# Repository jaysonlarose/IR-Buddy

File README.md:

# IR-Buddy

A Thing That Does IR Remote Stuff.

## Easy To Use

IR-Buddy presents itself to a host computer as a USB Serial device and uses a simple, straightforward ASCII protocol. You can open up the device using a terminal emulator and get started right away, or you can build it into an automation system. Capturing and replaying an IR code is as easy as pointing the remote at IR-Buddy, hitting the button, and copy-pasting the output back into the terminal.

## Smart, But Not Too Smart

IR-Buddy has a couple of power features for those that want to use them. It understands the concept of codes that repeat a certain sequence when the button is held down, to make tasks like changing volume go more smoothly. The output frequency can be tweaked to a certain extent to satisfy receivers that may be slightly finicky. It has screw terminals to accept up to eight emitter LEDs, which can be individually enabled or disabled, handy for when you have multiple devices that react to the same code. All of these features are completely optional.

What do I mean by "not too smart"? IR-buddy doesn't have a concept of what *type* of code it's sending or receiving. It doesn't know NEC protocol from JVC protocol from RC5. It just sees a bunch of ON-OFF transitions, and that's what it gives you. When you want to send a code, you tell it the timing of how to send these ON-OFF transitions, and it'll do it. If you want to get fancy with interpreting or synthesizing these ON-OFF timing pairs, that's your prerogative.

## Protocol Details

IR-buddy communicates as a standard USB Serial device using the ASCII character set. Line termination is UNIX-style, using just the linefeed character (0x0a). You may need to fiddle around with your terminal emulator software to get this dialed in.

### IR Reception

Whenever IR-Buddy isn't actively receiving a code to send or sending one, it's monitoring the IR receiver for activity. When it finishes receiving one, it will print out a message that looks like this:

```
IR <ondur> <offdur> <ondur> <offdur> <...> <ondur>\n
```

`<ondur>` is the length of time that the modulated IR carrier was detected ("MARK" time), in microseconds.

`<offdur>` is the length of time that the modulated IR carrier was absent ("SPACE" time), in microseconds.

Example

I've got a CRT TV. It's an Advent somethingorother that I bought off eBay. It didn't come with a remote, so I had to buy one off eBay as well, but I digress. When I point the remote at the IR-buddy and give the power button a good press, I get:

```
IR 15866 450 1650 500 1650 500 1650 500 550 500 550 500 550 500 1650 500 550 500 550 500 1650 500 550 500 550 500 550 450 600 500 550 500 550 600
IR 22850 500 1650 450 1700 500 1650 500 500 500 550 500 550 500 1650 500 550 500 550 500 1650 500 550 500 550 500 550 500 550 500 550 500 550 600
IR 22800 500 1650 500 1650 500 1650 500 550 500 550 500 550 500 1650 500 550 500 550 500 1650 500 550 500 550 500 550 450 600 500 550 500 500 650
IR 22800 500 1650 500 1650 500 1650 500 550 500 550 500 550 500 1650 500 500 500 550 500 1650 500 550 500 550 500 550 500 550 500 550 500 550 600
IR 22850 500 1650 500 1650 500 1650 500 550 500 500 500 550 500 1650 500 550 500 550 500 1650 500 550 500 550 500 550 500 550 500 550 500 550 600
```

(And the TV turns on.) Yes, five separate lines. Remote controls tend to be fairly chatty when you press the button, and the Arduino-IRremote library that powers IR-buddy splits out any code sequence with a gap longer than about 5 milliseconds into a separate transmission.

What you're looking at is a list of timings. All values are in microseconds.

The first number after "IR" is the amount of time since the end of the last detected transmission. This is provided for when you need to combine multiple transmissions together into a single code. I happen to know a bit about this TV, and that's exactly what we're going to need to do here, as I'll explain in a bit. But first, let's discuss the rest of the line.

The next number is the "mark" time. The number of microseconds that the 38KHz infrared carrier was detected. The next number is the "space" time, the duration of time that no carrier is being sent. After that is another "mark" time. Then another "space" time. And so on.

As I mentioned, I know a bit about this TV, and I know that you need to send a code at least twice to get it to pay attention to you. So we're going to combine two of these codes together. Take the first line, and remove the "IR" from the start of it along with the first number. Then, take the second line (minus the initial "IR") and add it to the end of the first line, like so:

```
1650 500 1650 500 1650 500 550 500 550 500 550 500 1650 500 550 500 550 500 1650 500 550 500 550 500 550 450 600 500 550 500 550 600 22850 500 1650 450 1700 500 1650 500 500 500 550 500 550 500 1650 500 550 500 550 500 1650 500 550 500 550 500 550 500 550 500 550 500 550 600
```

Copy and paste this line back into the terminal emulator. You may need to press "enter" at the end as well. You should get back a line saying "RX OK". And if you're me, your TV will turn back off.

### IR Transmission

Well, we already sent our first IR code in the previous section, but I'll go into more detail here. In its simplest form, sending an IR code is just a matter of entering a quantity of "on duration", "off duration" numbers, separated by spaces, followed by a newline (aka pressing "return").

As soon as you enter a numeric character, IR-buddy will print out "RX " followed by the quantity of timing values entered thusfar. Each time you press space to start a new timing value, it will update the quantity. When you press return, it will respond with "OK" followed by a newline and transmit the code.

#### Repeat Codes

Most remotes have some sort of method of telling the thing on the other end of the room that a button is being held down. Sure, you can just send the code over and over again, but it just won't be as seamless as being able to act like the original. That's where repeat codes come in.

A ton of remotes use what's called the NEC protocol (or one of derivatives of the NEC protocol). Long story short, codes start with a 9 millisecond "attention" mark, followed by 4.5 milliseconds of space, then approximately 54 milliseconds of the actual remote data. As long as the button that initiated the code is held down, the remote announces this by sending an additional set of (9ms mark, 2.25ms space, 560 microsecond mark) every 110 milliseconds.

Here's what this looks like from IR-Buddy's perspective, using the "volume up" button on an old LG television remote as an example:

```
IR 434500 9050 4500 600 500 600 550 600 1650 600 500 600 550 600 550 600 500 600 550 600 1650 600 1650 600 500 600 1650 600 1650 600 1650 600 1650 600 1650 600 550 600 1650 600 550 600 500 600 550 600 500 600 550 600 550 600 1650 600 500 600 1650 600 1650 600 1650 600 1650 600 1650 600 1650 600
IR 40200 9050 2250 600
IR 96500 9100 2200 600
IR 96500 9100 2200 600
IR 96550 9050 2250 600
IR 96500 9050 2250 600
```

Just like the protocol describes, we see a bunch of data, followed by about 40 milliseconds of silence. Then we see the first repeat burst, followed by about 96 milliseconds of silence, then the next, and so on, and so forth.

Instructing IR-Buddy to send a code along with a repeat sequence looks like this:

```
<ondur> <offdur> <ondur> <offdur> ... <ondur> <offdur> R <ondur> <offdur> ... <ondur> <offdur>
```

So, a set of mark/space timings, ending with space, followed by "R", followed by another set of mark/space timings, ending with space.

IR-buddy will send the first set of timings, and then repeat the second set of timings until it receives another character from the terminal. It will respond with "REPEAT" instead of "OK" to announce this. When you want the repeating to stop, send any character to IR-buddy. It will respond with "OK", and return to normal operations.

Returning back to the LG volume key, this is what we'll paste to replicate its behavior:

```
9050 4500 600 500 600 550 600 1650 600 500 600 550 600 550 600 500 600 550 600 1650 600 1650 600 500 600 1650 600 1650 600 1650 600 1650 600 1650 600 550 600 1650 600 550 600 500 600 550 600 500 600 550 600 550 600 1650 600 500 600 1650 600 1650 600 1650 600 1650 600 1650 600 1650 600 40200 R 9050 2250 600 96500
```

To explain how to construct this... Take the first line we received and throw away the first value, like we've done before. The code we've got so far ends on a mark. When not using repeat codes, IR-buddy is lenient and doesn't care whether you end on a mark or a space, but when using repeat codes you always need to end on a space. So we tack the 40 milliseconds of space from the next portion of the code onto the end of what we've got so far, and then follow it up with the "R" repeat declaration. This will take care of that weirdly timed first repeat burst, so all we need to add after the repeat declaration is the 9050 mark, 2250 space, 600 mark and finally ending with the 96500 space to finish up the 110ms repeat.

#### Output LED Muxing

You may have noticed that there are separate screw terminals for attaching infrared LEDS to, and that each one has a little number next to it, from 1 to 8. This isn't just so you can spam your remote codes in all directions at once, though you *can* use it that way, if you want.

Or, consider this scenario: You've got three of the same model of TV sitting in the same room, and you only want to control a specific television while leaving the other two alone. That's exactly what setting the LED mux is for.

Using a pair of wires, you can run a LED from each of the terminals to its own dedicated television, taping it to the IR receiver with something like duct tape to ensure that each television only sees the LED that's attached to it. You can then specify which LED — or combination of LEDs — that you want a particular code to be sent to.

To make our example easy, let's say that TV 1 is being serviced by the LED in terminal 1, TV 2 by terminal 2, and TV 3 by terminal 3. Now we just want to send a code to TV 2.

Pin muxing is handled by an 8-bit binary value. Terminal 1 is activated by bit 0, terminal 2 by bit 1, terminal 3 by bit 2... all the way up to terminal 8, activated by bit 7:

| Terminal Label | Bit Number | Decimal Value |
| -------------- | ---------- | ------------- |
| 1              | 0          | 1             |
| 2              | 1          | 2             |
| 3              | 2          | 4             |
| 4              | 3          | 8             |
| 5              | 4          | 16            |
| 6              | 5          | 32            |
| 7              | 6          | 64            |
| 8              | 7          | 128           |

Specifying a mux value to use for a particular code is done by prepending the code with the mux value followed by the mux designator, "M":

```
<muxval> M <ondur> <offdur> <ondur> <offdur> ... <ondur>
```

The value is specified in decimal. So, sending a code just to our hypothetical TV 2 will look like:

```
2 M 9050 4500 600 500 600 550 etc
```

To send to TV 1 and 3 but not 2:

```
5 M 9050 4500 600 500 600 550 etc
```

To send to every terminal except our three televisions:

```
248 M 9050 4500 600 500 600 550 etc
```

The default is a mux value of 255, as in all terminals are used. You can set a muxval if 0 if you *really* want to, but of course no code will make it out.

#### Output Frequency Tweaking

As alluded to previously, the vast majority of remote controls operate using a carrier frequency of 38 KHz, meaning that a mark timing isn't comprised of just shining the LED for a duration of time, but instead is made by blinking the LED on and off 38,000 times per second. If, for whatever reason, you need a different output frequency, you can change this on a per-code basis by using the "F" frequency declaration.

Setting the default 38 KHz frequency would look like:

```
38 F 9050 4500 600 500 600 550 etc
```

Another popular frequency is 40 KHz. Most devices that expect 40KHz will respond just fine to 38KHz, but if you've got a finnicky device, then you can try 40 KHz like so:

```
40 F 9050 4500 600 500 600 550 etc
```

To be fully honest, this is just passing through the functionality that was provided by what few remnants of the original Arduino-IRremote libarary remain, and I'm just providing it in case somebody needs it.

### Switching between "ANSI" and "ASCII" output

By default, IR-Buddy does some trickery with ANSI escape codes to display the running count of timing values entered. If you don't like this for whatever reason, you can switch between ANSI output, straight ASCII output, and back by sending "A".

### Binary protocol

Maybe only using 7 out of every 8 bits isn't your style. Maybe you want something a tiny bit more machine-readable. If so, then the binary protocol might be right up your alley!

#### Opcodes

| opcode name     | hex value |
| --------------- | --------- |
| OP_IR_TRANSMIT  | 0x01      |
| OP_IR_RECEIVE   | 0x02      |
| OP_EXIT_BINARY  | 0x03      |
| OP_ACK          | 0x04      |
| OP_NAK          | 0x05      |
| OP_REPEATING    | 0x06      |
| OP_ENTER_BINARY | 0xff      |

All opcodes are kind of mushed together. Some of these (OP_IR_TRANSMIT, OP_ENTER_BINARY, OP_EXIT_BINARY) are sent *to* ir-buddy to request an action. Some (OP_IR_RECEIVE) are sent *from* ir-buddy to announce events. Some (OP_ACK, OP_NAK, OP_REPEATING) are sent from ir-buddy to announce the completion status of a request.

#### Timing division

Timing values are expressed using 16 bit unsigned integers (this is also how they're stored internally, well, for the most part). Normally this would only give you values between 0 and 65,535 microseconds, which is not long enough for many timing durations, so all of these values are divided by 10. This happens in the background and is transparent to you in ASCII mode, but that isn't the case for binary mode since we're using 16 bit unsigned integers here, too. So when you're transmitting a code, be sure to divide each of the timing values by 10 first, and whenever you're receiving a code, expect that you'll need to multiply each of the timing values you receive by 10.

#### Switching to Binary Protocol

Send OP_ENTER_BINARY. Expect a response of OP_ACK.

#### Returning back to ASCII/ANSI Protocol

Send OP_EXIT_BINARY (which is also the equivalent of entering CTRL+C repeatedly at a terminal) until you start getting ASCII "CANCEL" responses.

#### Sending an IR code

This one's a whole-ass packet.

| Name           | Length              | Description                                                                   |
| -------------- | ------------------- | ----------------------------------------------------------------------------- |
| OP_IR_TRANSMIT | 8 bits              | Tells IR-Buddy that you want to send an IR code                               |
| mux            | 8 bits              | mux value                                                                     |
| freq           | 8 bits              | transmit frequency (KHz)                                                      |
| codelen        | 16 bits             | quantity of values comprising the timings for the non-repeat part of the code |
| repeatlen      | 16 bits             | quantity of values comprising the timings for the repeating part of the code  |
| code timings   | 16 bits x codelen   | divided timing values for the non-repeat part of the code                     |
| repeat timings | 16 bits x repeatlen | divided timing values for the repeating part of the code                      |

All 16-bit values are big-endian bit order, i.e., you send the high byte followed by the low byte.

Remember that all timing values should be divided by 10 before they're converted to 16 bit values.

IR-buddy will respond with OP_ACK for codes that don't have a repeat section, or OP_REPEATING for codes that do. The code will repeat until you send a byte of data (the contents of which don't matter), after which IR-buddy will send back OP_ACK.

#### Receiving an IR code

| Name          | Length            | Description                                       |
| ------------- | ----------------- | ------------------------------------------------- |
| OP_IR_RECEIVE | 8 bits            | IR-Buddy announcing it's about to send an IR code |
| codelen       | 16 bits           | quantity of timing values that are to follow      |
| code timings  | 16 bits x codelen | divided timing values                             |

All 16-bit values are big-endian bit order, meaning you'll receive the high byte followed by the low byte.

Remember that all timing values are divided by 10, so you'll need to multiply them by 10 afterwards.

## Making Your Own

Inside the "board" subdirectory, you'll find the KiCad project, schematic, PCB layout, and associated library components, along with "bom.txt", which is the Bill of Materials. If you want to skip messing around with all the KiCad stuff, then you can upload "board/gerbers/gerbers.zip" to your favorite PCB manufacturing house.

Each of the eight IR emitters has its own section, which consists of a screw terminal, a resistor, and a BS170 transistor. The above diagram shows which components are associated with each other.

Note that in the Bill of Materials, the quantity of screw terminals, transistors, resistors, and LEDs is variable. If you only intend to use a single IR LED emitter, then of course it doesn't make any sense for you to populate the other 7 slots.

The BS170 transistor in the center of the board connects the microcontroller's IR output pin to the source of all of the other transistors, so it is mandatory. Likewise, IR reception will obviously not work if you don't solder in the IR receiver.

Here's an example of a minimum-configuration IR-Buddy.

### Building and Installing the Firmware

#### Using arduino-mk

The development enviroment I use for building "Arduino" firmware is made up of a Debian-based Linux distribution with the "arduino" and "arduino-mk" packages installed. If you're familiar with what this is, then you should be basically good to go. Plug in the Sparkfun Pro Micro via USB, check `dmesg` to see what /dev entry it got assigned, update Makefile to match, run `make` and `make upload`.

#### Using the Arduino IDE

I've tweaked the file and directory names in such a way that this will work in the Arduino IDE as well. 

* Plug the Sparkfun Pro Micro board in via USB.
* Menu to "File -> Open". Navigate to and open firmware/firmware.ino.
* Menu to "Tools -> Board -> Arduino AVR Boards" and select "Arduino Leonardo".
* Menu to "Port" and choose the appropriate port that the Pro Micro board is on.
* Click the "Verify" button to build. Ignore the "Low memory available. stability problems may occur." warning.
* Click the "Upload" button.

#### Uploading the Provided .hex File Using Avrdude

Or, if you're happy with the firmware as I built it and are slightly hardcore, you can just upload the firmware_.hex file that this repository ships with and call it a day.

* Plug the Sparkfun Pro Micro board in via USB.
* Doubleclick the board's reset button to put it into firmware update mode.
* Run something very similar to the following:

```bash
avrdude -q -V -p atmega32u4 -C /etc/avrdude.conf -D -c avr109 -b 57600 -P /dev/ttyACM2 -U flash:w:firmware_.hex:i
```

I say "similar to" because I don't know where your avrdude.conf file is located, nor do I know how to refer to the serial port that the Pro Micro board will show up as.

## License

At the end of the day, this is all just a bunch of bits. I don't care what you do with it. I also take no responsibility for what you do with it. Except for anything in the lib/firmware directory. Those bits, heavily modified as they may be, have had a software license attached to them.

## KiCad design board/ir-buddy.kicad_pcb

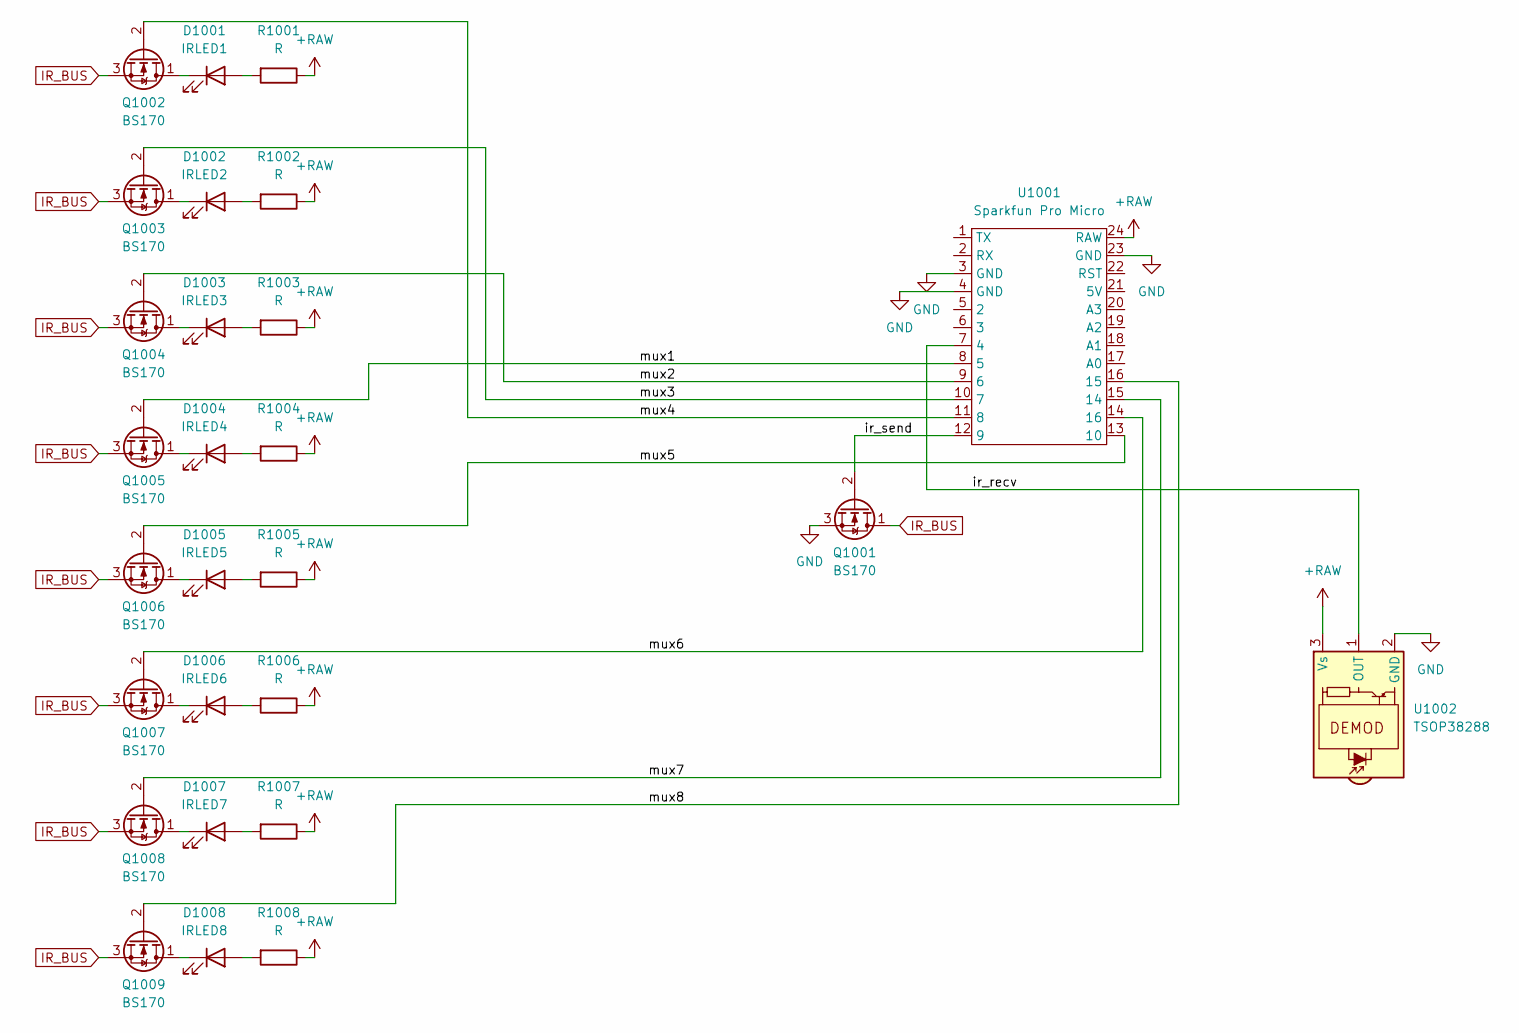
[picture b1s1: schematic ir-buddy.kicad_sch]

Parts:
D1001: IRLED1; Screw_Terminal_2.54mm_x_2
D1002: IRLED2; Screw_Terminal_2.54mm_x_2
D1003: IRLED3; Screw_Terminal_2.54mm_x_2
D1004: IRLED4; Screw_Terminal_2.54mm_x_2
D1005: IRLED5; Screw_Terminal_2.54mm_x_2
D1006: IRLED6; Screw_Terminal_2.54mm_x_2
D1007: IRLED7; Screw_Terminal_2.54mm_x_2
D1008: IRLED8; Screw_Terminal_2.54mm_x_2
Q1001, Q1002, Q1003, Q1004, Q1005, Q1006, Q1007, Q1008, Q1009: BS170; TO-92_Inline_spread_pins
R1001, R1002, R1003, R1004, R1005, R1006, R1007, R1008: R; R_Axial_DIN0204_L3.6mm_D1.6mm_P7.62mm_Horizontal
U1001: Sparkfun Pro Micro; Sparkfun_Pro_Micro
U1002: TSOP38288; Vishay_MINICAST-3Pin

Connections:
+RAW: R1001.1, R1002.1, R1003.1, R1004.1, R1005.1, R1006.1, R1007.1, R1008.1, U1001.24 (RAW), U1002.3 (Vs)
/ir_recv: U1001.7 (4), U1002.1 (OUT)
/ir_send: Q1001.2 (G), U1001.12 (9)
/mux1: Q1005.2 (G), U1001.8 (5)
/mux2: Q1004.2 (G), U1001.9 (6)
/mux3: Q1003.2 (G), U1001.10 (7)
/mux4: Q1002.2 (G), U1001.11 (8)
/mux5: Q1006.2 (G), U1001.13 (10)
/mux6: Q1007.2 (G), U1001.14 (16)
/mux7: Q1008.2 (G), U1001.15 (14)
/mux8: Q1009.2 (G), U1001.16 (15)
GND: Q1001.3 (S), U1001.3 (GND), U1001.4 (GND), U1001.23 (GND), U1002.2 (GND)
IR_BUS: Q1001.1 (D), Q1002.3 (S), Q1003.3 (S), Q1004.3 (S), Q1005.3 (S), Q1006.3 (S), Q1007.3 (S), Q1008.3 (S), Q1009.3 (S)
unnamed: D1001.2 (A), R1001.2
unnamed: D1001.1 (K), Q1002.1 (D)
unnamed: D1002.2 (A), R1002.2
unnamed: D1002.1 (K), Q1003.1 (D)
unnamed: D1003.2 (A), R1003.2
unnamed: D1003.1 (K), Q1004.1 (D)
unnamed: D1004.2 (A), R1004.2
unnamed: D1004.1 (K), Q1005.1 (D)
unnamed: D1005.2 (A), R1005.2
unnamed: D1005.1 (K), Q1006.1 (D)
unnamed: D1006.2 (A), R1006.2
unnamed: D1006.1 (K), Q1007.1 (D)
unnamed: D1007.2 (A), R1007.2
unnamed: D1007.1 (K), Q1008.1 (D)
unnamed: D1008.2 (A), R1008.2
unnamed: D1008.1 (K), Q1009.1 (D)

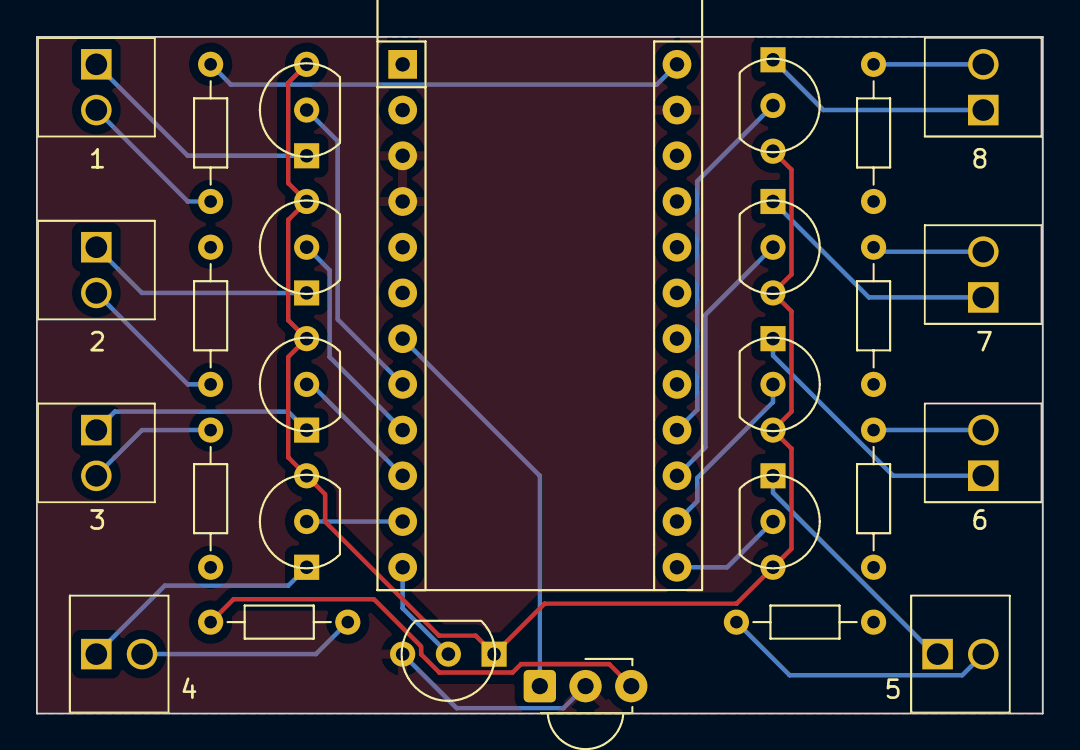
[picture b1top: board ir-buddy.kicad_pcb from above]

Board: 2 copper layers, 55.9 x 37.6 mm, 27 parts (0 on the bottom side), 29 nets.

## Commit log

2026-02-27 Initial commit of combined project
2026-02-27 * Added a background to board diagram.svg.
2026-02-28 * Added a .gitignore file. * Renamed many files in the firmware subdirectory to make things compatible with Arduino IDE. * Improved instructions for building and loading the firmware.
2026-02-28 * documentation typo fix
2026-03-05 * Removed a vestigal variable from a misguided feature addition attempt.
2026-03-06 * Fixed a minor timing issue with repeating codes
2026-03-06 There. Timing really fixed. I hope.
2026-03-06 * cleanup
2026-05-12 * Fixed a bug where the microcontroller would come up with the IR LEDs active. * Added a DEBUG_MUX preprocessor directive. * Fixed the mux pin assignments. Oops.
